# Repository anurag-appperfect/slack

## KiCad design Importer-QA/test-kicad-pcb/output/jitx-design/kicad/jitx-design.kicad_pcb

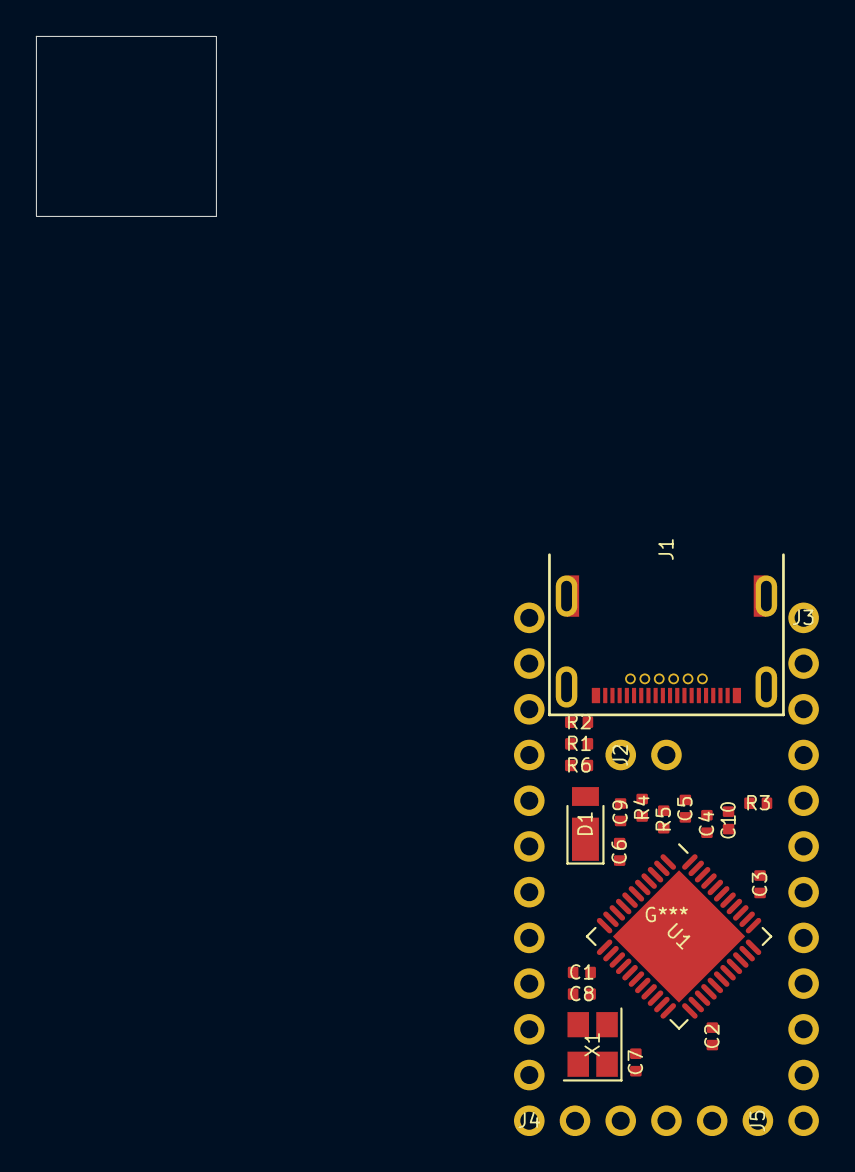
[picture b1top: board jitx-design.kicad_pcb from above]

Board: 4 copper layers, 24 parts (0 on the bottom side), 37 nets, no tracks yet.

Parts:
C1, C2, C3, C4, C5, C6, C7, C8, C9, C10: c_0402_1005metric_lp
D1: d_powerdi_123_lp
J1: cx70m_24p1_lp
J2: pins2_lp
J3, J4: pins12_lp
J5: pins5_lp
R1, R2, R3, R4, R5, R6: r_0402_1005metric_lp
U1: qfn_44_1ep_7x7mm_p05mm_ep52x52mm_lp
X1: crystal_smd_seikoepson_fa238_4pin_32x25mm_lp

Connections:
D+: J1.A6, J1.B6, J2.1, R4.2
D-: J1.A7, J1.B7, J2.2, R5.2
GND: C1.2, C2.2, C3.2, C4.2, C5.2, C6.2, C7.2, C8.2, C9.2, C10.2, J1.1, J1.2, J1.3, J1.4, J1.5, J1.6, J1.7, J1.A1, J1.A12, J1.B1, J1.B12, J1.S1, J3.2, J4.9, J4.10, R1.1, R2.1, R6.1, U1.5, U1.15, U1.23, U1.33, U1.35, U1.43, U1.45, X1.2, X1.4
Net-C7-Pad1: C7.1, U1.17, X1.1
Net-C8-Pad1: C8.1, U1.16, X1.3
Net-C9-Pad1: C9.1, U1.6
Net-C10-Pad1: C10.1, U1.42
Net-J1-PadA5: J1.A5, R1.2
Net-J1-PadB5: J1.B5, R2.2
Net-R4-Pad1: R4.1, U1.4
Net-R5-Pad1: R5.1, U1.3
PB1: J3.9, U1.9
PB2: J3.11, U1.10
PB3: J3.10, U1.11
PB4: J4.2, U1.28
PB5: J4.1, U1.29
PB6: J3.12, U1.30
PB7: J5.5, U1.12
PC6: J4.5, U1.31
PC7: J5.3, U1.32
PD0: J4.7, U1.18
PD1: J4.8, U1.19
PD2: J4.11, U1.20
PD3: J4.12, U1.21
PD4: J4.6, U1.25
PD5: J5.4, U1.22
PD7: J4.4, U1.27
PE6: J4.3, U1.1
PF0: J5.1, U1.41
PF1: J5.2, U1.40
PF4: J3.5, U1.39
PF5: J3.6, U1.38
PF6: J3.7, U1.37
PF7: J3.8, U1.36
RESET: J3.3, R3.1, U1.13
VBUS: C5.1, C6.1, D1.2, J1.A4, J1.A9, J1.B4, J1.B9, J3.1, R6.2, U1.2, U1.7
VCC: C1.1, C2.1, C3.1, C4.1, D1.1, J3.4, R3.2, U1.14, U1.24, U1.34, U1.44

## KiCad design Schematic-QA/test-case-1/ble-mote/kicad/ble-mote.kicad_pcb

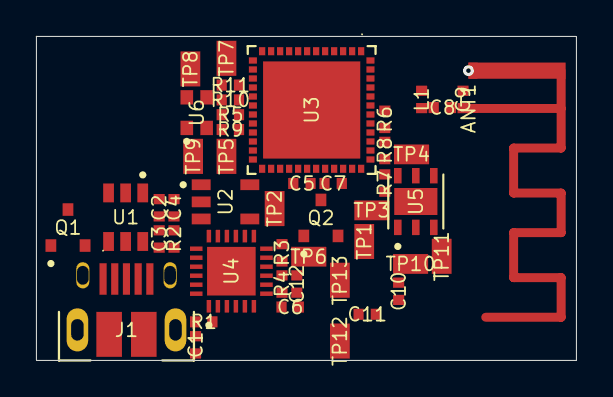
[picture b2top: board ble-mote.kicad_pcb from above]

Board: 4 copper layers, 30.0 x 18.0 mm, 48 parts (1 on the bottom side), 30 nets.

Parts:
ANT1: ant_2GHz4_inverted_f_geom
C1, C2, C3, C4, C5, C6, C7, C8, C9, C10, C11, C12: ipc_two_pin_landpattern
J1: amphenol_10103594_0001lf
J2: amphenol_minitek127_pkg
L1: ipc_two_pin_landpattern
Q1, Q2: SOT95P280X100_3N
R1, R2, R3, R4, R5, R6, R7, R8, R9, R10, R11: ipc_two_pin_landpattern
TP1, TP2, TP3, TP4, TP5, TP6, TP7, TP8, TP9, TP10, TP11, TP12, TP13: rc_landpattern
U1: SOT95P280X145_6N
U2: SOT95P280X145_5N
U3: pqfn50p700x700x104_49n
U4: qfn_landpattern
U5: son100p300x300x80_7n
U6: rgb_2020

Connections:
D+: J1.3, U1.5, U4.3
D-: J1.2, U1.6, U4.4
DTR_ECI: Q2.2, R2.1, U4.15
EN: Q1.3, TP5.p, U3.9
ESP-RX: TP2.p, U3.40, U4.13
ESP-TX: TP1.p, U3.41, U4.12
H-I2C_scl: R8.1, TP4.p, U3.36, U5.6
H-I2C_sda: R7.1, TP3.p, U3.39, U5.1
LNA-IN: C8.1, L1.2, U3.2
P3V3: C5.2, C6.2, C7.2, C10.2, C11.2, C12.2, R4.2, R5.1, R6.1, R7.2, R8.2, TP10.p, U2.5, U3.1, U3.3, U3.4, U3.19, U3.37, U3.43, U3.46, U4.5, U4.6, U4.7, U5.5, U6.3
P5V0: C3.1, C4.2, J2.1, J2.2, TP9.p, U1.4, U2.1, U2.3, U4.8
PC-RESET: J2.6, R6.2, U3.42
PC-RX: J2.8, TP8.p, U3.10
PC-SET: J2.9, R5.2, U3.38
PC-TX: J2.10, TP7.p, U3.11
RTS_ECI: Q1.2, R3.1, U4.11
VBUS: C2.1, J1.1, U1.1, U1.3
b: Q1.1, R2.2
c: Q2.3, TP6.p, U3.23
g: R10.2, U6.4
gnd: ANT1.gnd, C1.2, C2.2, C3.2, C4.1, C5.1, C6.1, C7.1, C9.1, C10.1, C11.1, C12.1, J1.5, J2.3, J2.4, L1.1, R1.2, TP11.p, TP12.p, TP13.p, U1.2, U2.2, U3.49, U4.2, U4.25, U5.2
l_b: R11.2, U6.2
launch: ANT1.launch, C8.2, C9.2
nRST: R4.1, U4.9
proc_q1_b: Q2.1, R3.2
pwm0_timer: R9.1, U3.16
pwm1_timer: R10.1, U3.15
pwm2_timer: R11.1, U3.14
r: R9.2, U6.1
rid_p1: C1.1, J1.6, J1.7, J1.8, J1.9, J1.10, J1.11, J1.13, J1.14, R1.1

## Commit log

2022-03-08 fvtv
2022-03-08 Update Jenkinsfile
